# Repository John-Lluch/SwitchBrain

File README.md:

_\[ find below the English translation \]_ 

# SwitchBrain

Documentos y otras utilidades relacionadas con el canal de YouTube del Computador a Relés,

## Canal de YouTube

[https://www.youtube.com/@RelayComputer](https://www.youtube.com/@RelayComputer)

## Enlaces útiles

Kicad EDA : [https://www.kicad.org](https://www.kicad.org)  
Logisim Evolution (simulador digital) edición HC : [https://github.com/kevinawalsh/logisim-evolution](https://github.com/kevinawalsh/logisim-evolution)  
CircuitJS1 (simulador analógico) versión online : [https://www.falstad.com/circuit/circuitjs.html](https://www.falstad.com/circuit/circuitjs.html)  
CircuitJS1 (simulador analógico) versión escritorio : [https://www.falstad.com/circuit/offline/](https://www.falstad.com/circuit/offline/)  

<br /><br />

----------------------------------------------------------------------------------------------------------

# SwitchBrain (English)

Documents and other utilities related with the Relay Computer Youtube Channel

## YouTube Channel

[https://www.youtube.com/@RelayComputer](https://www.youtube.com/@RelayComputer)

## Useful Links

Kicad EDA : [https://www.kicad.org](https://www.kicad.org)  
Logisim Evolution (digital simulator) HC edition : [https://github.com/kevinawalsh/logisim-evolution](https://github.com/kevinawalsh/logisim-evolution)  
CircuitJS1 (analog simulator) online version : [https://www.falstad.com/circuit/circuitjs.html](https://www.falstad.com/circuit/circuitjs.html)  
CircuitJS1 (analog simulator) desktop version : [https://www.falstad.com/circuit/offline/](https://www.falstad.com/circuit/offline/)

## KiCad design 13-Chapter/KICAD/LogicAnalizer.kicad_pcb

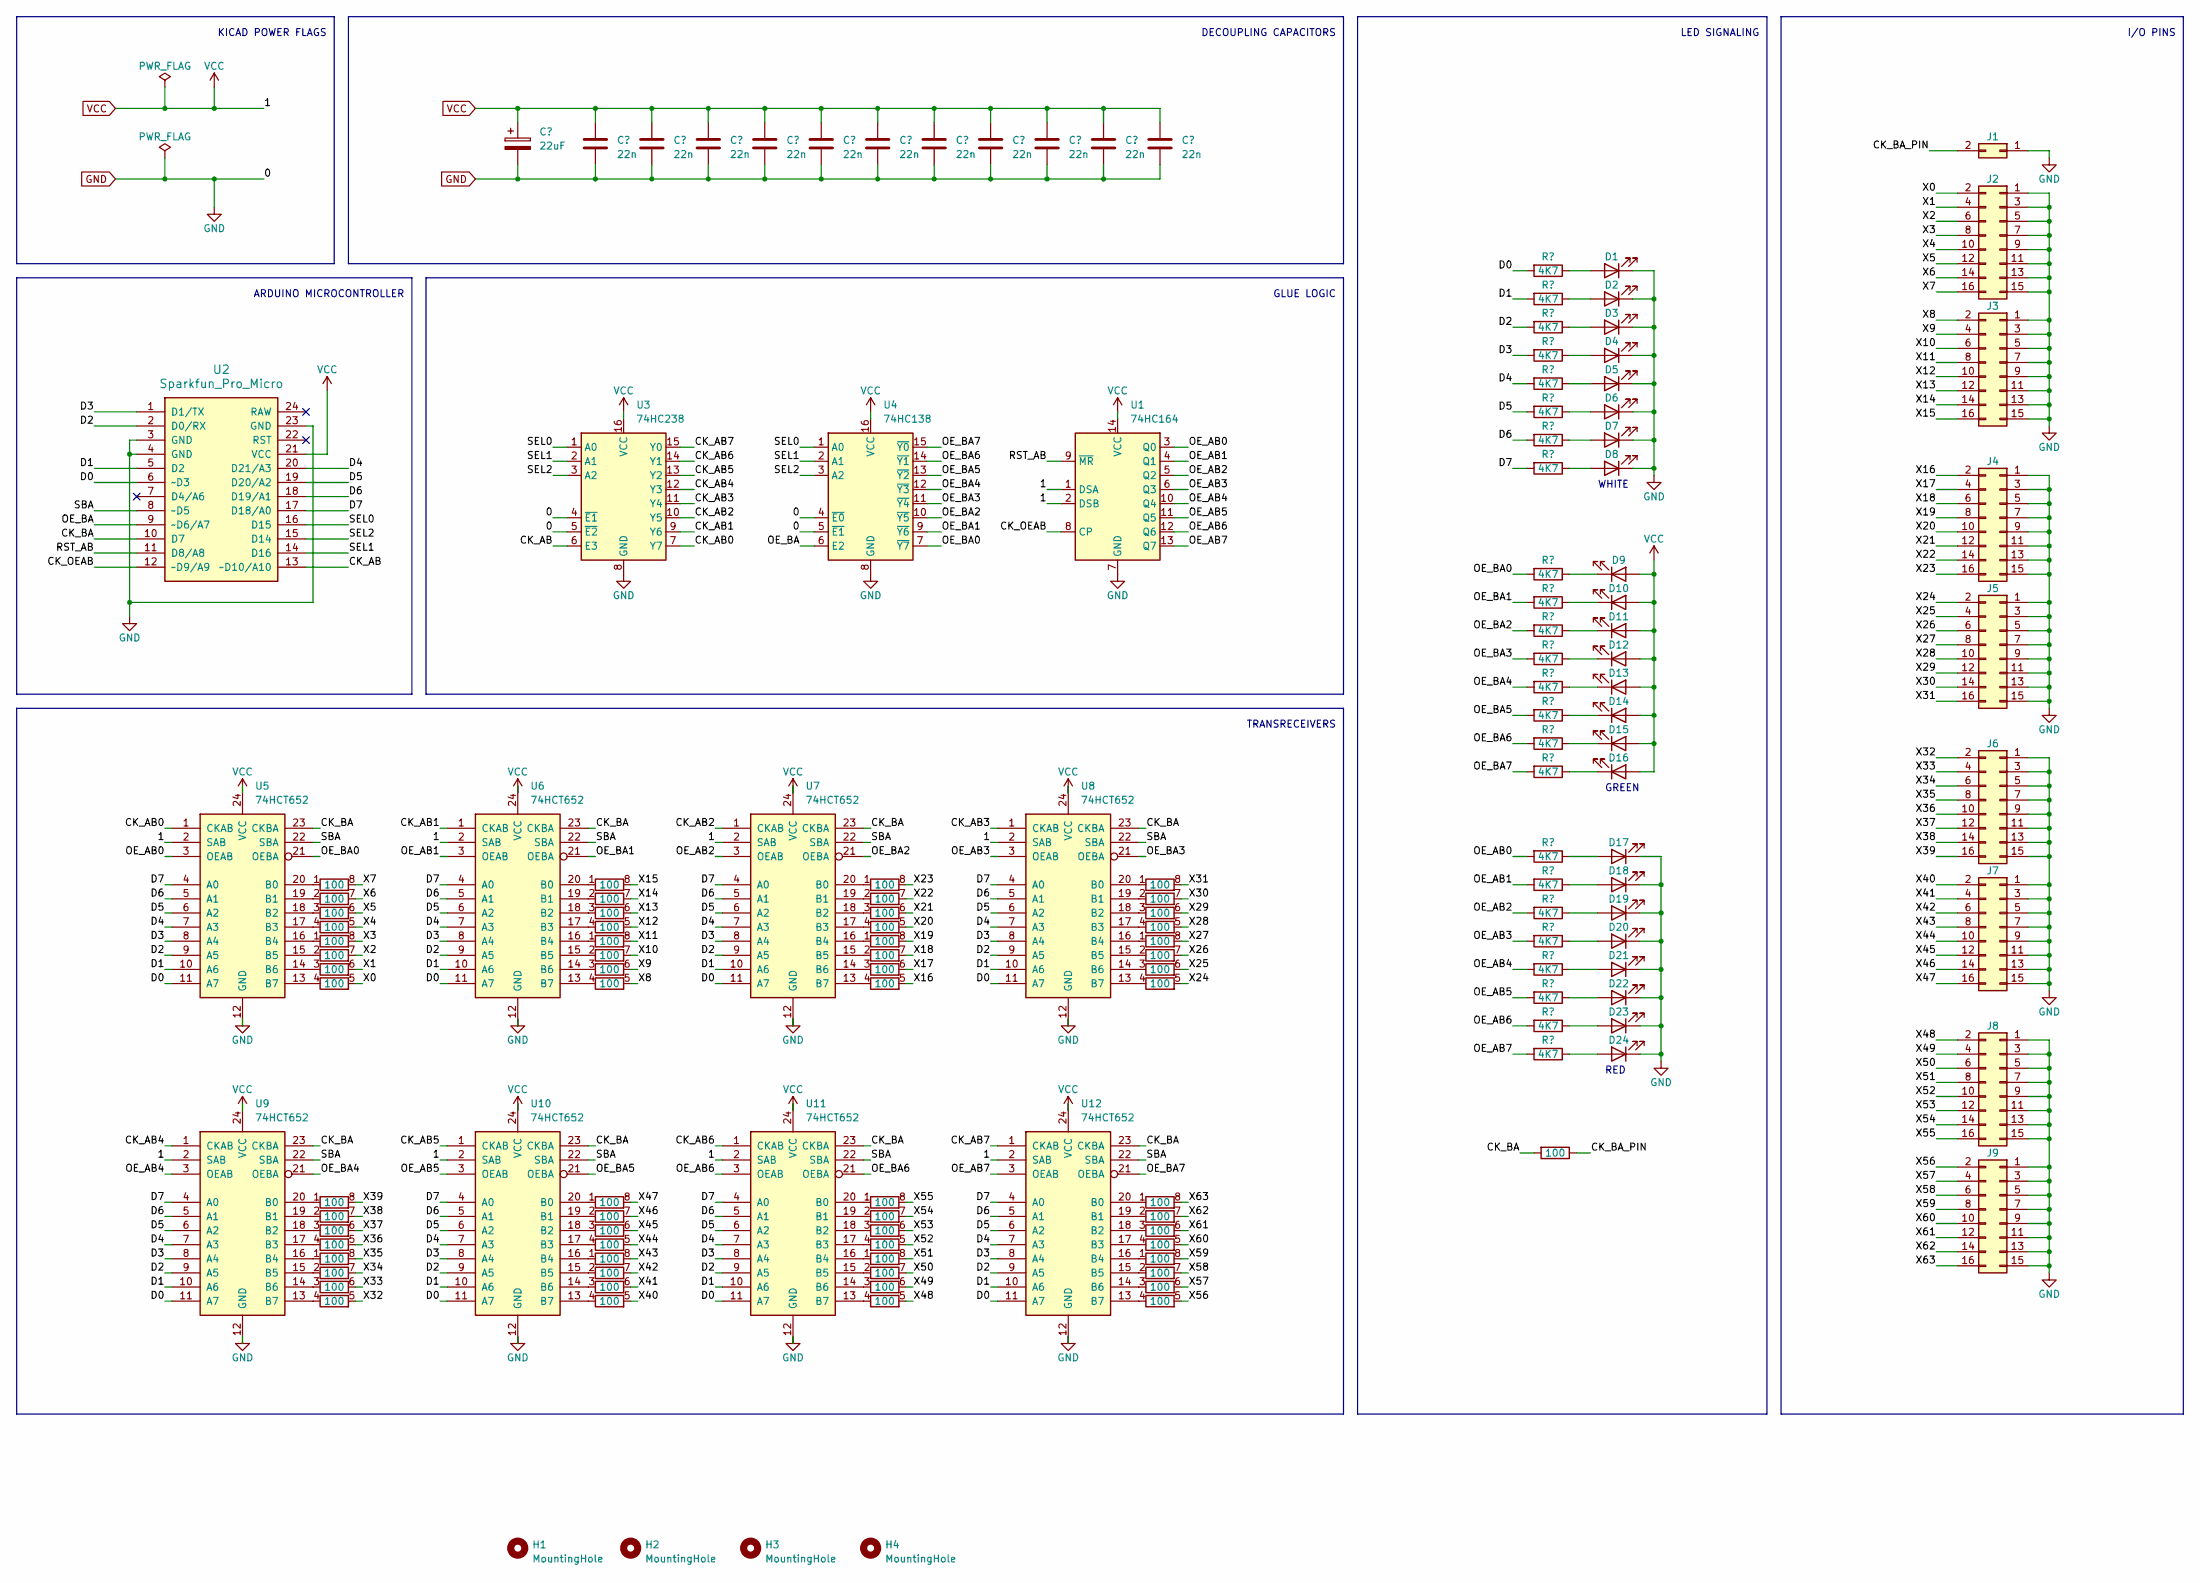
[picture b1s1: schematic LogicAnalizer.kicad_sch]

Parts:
C1: 22uF; CP_Radial_D5.0mm_P2.00mm
C2, C3, C4, C5, C6, C7, C8, C9, C10, C11, C12: 22n; C_0603_1608Metric; LCSC Part # C326840
D1, D2, D3, D4, D5, D6, D7, D8: LED; LED_0603_1608Metric; LCSC Part # C158100
D9, D10, D11, D12, D13, D14, D15, D16: LED; LED_0603_1608Metric; LCSC Part # C89809
D17, D18, D19, D20, D21, D22, D23, D24: LED; LED_0603_1608Metric; LCSC Part # C193902
H1, H2, H3, H4: MountingHole; MountingHole_3.2mm_M3_DIN965_Pad
J1: Conn_02x01; PinHeader_2x01_P2.54mm_Vertical
J2, J3, J4, J5, J6, J7, J8, J9: Conn_02x08_Odd_Even; PinHeader_2x08_P2.54mm_Vertical; LCSC Part # C24328
R1, R2, R3, R4, R5, R6, R7, R8, R9, R10, R11, R12, R13, R14, R15, R16, R17, R18, R19, R20, R21, R22, R23, R24: 4K7; Meu-R_0603_1608Metric; LCSC Part # C23162
R25: 100; Meu-R_0603_1608Metric; LCSC Part # C22775
RN1, RN2, RN3, RN4, RN5, RN6, RN7, RN8, RN9, RN10, RN11, RN12, RN13, RN14, RN15, RN16: 100; R_Array_Convex_4x0603; LCSC Part # C425240
U1: 74HC164; SO-14_3.9x8.65mm_P1.27mm; LCSC Part # C5419
U2: Sparkfun_Pro_Micro
U3: 74HC238; SOIC-16_3.9x9.9mm_P1.27mm; LCSC Part # C68225
U4: 74HC138; SOIC-16_3.9x9.9mm_P1.27mm; LCSC Part # C6818
U5, U6, U7, U8, U9, U10, U11, U12: 74HCT652; SOIC-24W_7.5x15.4mm_P1.27mm

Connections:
/CK_AB: U2.13 (~D10/A10), U3.6 (E3)
/CK_AB0: U3.7 (Y7), U5.1 (CKAB)
/CK_AB1: U3.9 (Y6), U6.1 (CKAB)
/CK_AB2: U3.10 (Y5), U7.1 (CKAB)
/CK_AB3: U3.11 (Y4), U8.1 (CKAB)
/CK_AB4: U3.12 (Y3), U9.1 (CKAB)
/CK_AB5: U3.13 (Y2), U10.1 (CKAB)
/CK_AB6: U3.14 (Y1), U11.1 (CKAB)
/CK_AB7: U3.15 (Y0), U12.1 (CKAB)
/CK_BA: R25.2, U2.10 (D7), U5.23 (CKBA), U6.23 (CKBA), U7.23 (CKBA), U8.23 (CKBA), U9.23 (CKBA), U10.23 (CKBA), U11.23 (CKBA), U12.23 (CKBA)
/CK_BA_PIN: J1.2, R25.1
/CK_OEAB: U1.8 (CP), U2.12 (~D9/A9)
/D0: R1.2, U2.6 (~D3), U5.11 (A7), U6.11 (A7), U7.11 (A7), U8.11 (A7), U9.11 (A7), U10.11 (A7), U11.11 (A7), U12.11 (A7)
/D1: R2.2, U2.5 (D2), U5.10 (A6), U6.10 (A6), U7.10 (A6), U8.10 (A6), U9.10 (A6), U10.10 (A6), U11.10 (A6), U12.10 (A6)
/D2: R3.2, U2.2 (D0/RX), U5.9 (A5), U6.9 (A5), U7.9 (A5), U8.9 (A5), U9.9 (A5), U10.9 (A5), U11.9 (A5), U12.9 (A5)
/D3: R4.2, U2.1 (D1/TX), U5.8 (A4), U6.8 (A4), U7.8 (A4), U8.8 (A4), U9.8 (A4), U10.8 (A4), U11.8 (A4), U12.8 (A4)
/D4: R5.2, U2.20 (D21/A3), U5.7 (A3), U6.7 (A3), U7.7 (A3), U8.7 (A3), U9.7 (A3), U10.7 (A3), U11.7 (A3), U12.7 (A3)
/D5: R6.2, U2.19 (D20/A2), U5.6 (A2), U6.6 (A2), U7.6 (A2), U8.6 (A2), U9.6 (A2), U10.6 (A2), U11.6 (A2), U12.6 (A2)
/D6: R7.2, U2.18 (D19/A1), U5.5 (A1), U6.5 (A1), U7.5 (A1), U8.5 (A1), U9.5 (A1), U10.5 (A1), U11.5 (A1), U12.5 (A1)
/D7: R8.2, U2.17 (D18/A0), U5.4 (A0), U6.4 (A0), U7.4 (A0), U8.4 (A0), U9.4 (A0), U10.4 (A0), U11.4 (A0), U12.4 (A0)
/OE_AB0: R17.2, U1.3 (Q0), U5.3 (OEAB)
/OE_AB1: R18.2, U1.4 (Q1), U6.3 (OEAB)
/OE_AB2: R19.2, U1.5 (Q2), U7.3 (OEAB)
/OE_AB3: R20.2, U1.6 (Q3), U8.3 (OEAB)
/OE_AB4: R21.2, U1.10 (Q4), U9.3 (OEAB)
/OE_AB5: R22.2, U1.11 (Q5), U10.3 (OEAB)
/OE_AB6: R23.2, U1.12 (Q6), U11.3 (OEAB)
/OE_AB7: R24.2, U1.13 (Q7), U12.3 (OEAB)
/OE_BA: U2.9 (~D6/A7), U4.6 (E2)
/OE_BA0: R9.2, U4.7 (~Y7), U5.21 (OEBA)
/OE_BA1: R10.2, U4.9 (~Y6), U6.21 (OEBA)
/OE_BA2: R11.2, U4.10 (~Y5), U7.21 (OEBA)
/OE_BA3: R12.2, U4.11 (~Y4), U8.21 (OEBA)
/OE_BA4: R13.2, U4.12 (~Y3), U9.21 (OEBA)
/OE_BA5: R14.2, U4.13 (~Y2), U10.21 (OEBA)
/OE_BA6: R15.2, U4.14 (~Y1), U11.21 (OEBA)
/OE_BA7: R16.2, U4.15 (~Y0), U12.21 (OEBA)
/RST_AB: U1.9 (~MR), U2.11 (D8/A8)
/SBA: U2.8 (~D5), U5.22 (SBA), U6.22 (SBA), U7.22 (SBA), U8.22 (SBA), U9.22 (SBA), U10.22 (SBA), U11.22 (SBA), U12.22 (SBA)
/SEL0: U2.16 (D15), U3.1 (A0), U4.1 (A0)
/SEL1: U2.14 (D16), U3.2 (A1), U4.2 (A1)
/SEL2: U2.15 (D14), U3.3 (A2), U4.3 (A2)
/X0: J2.2, RN5.5 (R4.2)
/X1: J2.4, RN5.6 (R3.2)
/X2: J2.6, RN5.7 (R2.2)
/X3: J2.8, RN5.8 (R1.2)
/X4: J2.10, RN1.5 (R4.2)
/X5: J2.12, RN1.6 (R3.2)
/X6: J2.14, RN1.7 (R2.2)
/X7: J2.16, RN1.8 (R1.2)
/X8: J3.2, RN6.5 (R4.2)
/X9: J3.4, RN6.6 (R3.2)
/X10: J3.6, RN6.7 (R2.2)
/X11: J3.8, RN6.8 (R1.2)
/X12: J3.10, RN2.5 (R4.2)
/X13: J3.12, RN2.6 (R3.2)
/X14: J3.14, RN2.7 (R2.2)
/X15: J3.16, RN2.8 (R1.2)
/X16: J4.2, RN7.5 (R4.2)
/X17: J4.4, RN7.6 (R3.2)
/X18: J4.6, RN7.7 (R2.2)
/X19: J4.8, RN7.8 (R1.2)
/X20: J4.10, RN3.5 (R4.2)
/X21: J4.12, RN3.6 (R3.2)
/X22: J4.14, RN3.7 (R2.2)
/X23: J4.16, RN3.8 (R1.2)
/X24: J5.2, RN8.5 (R4.2)
/X25: J5.4, RN8.6 (R3.2)
/X26: J5.6, RN8.7 (R2.2)
/X27: J5.8, RN8.8 (R1.2)
/X28: J5.10, RN4.5 (R4.2)
/X29: J5.12, RN4.6 (R3.2)
/X30: J5.14, RN4.7 (R2.2)
/X31: J5.16, RN4.8 (R1.2)
/X32: J6.2, RN13.5 (R4.2)
/X33: J6.4, RN13.6 (R3.2)
/X34: J6.6, RN13.7 (R2.2)
/X35: J6.8, RN13.8 (R1.2)
/X36: J6.10, RN9.5 (R4.2)
/X37: J6.12, RN9.6 (R3.2)
/X38: J6.14, RN9.7 (R2.2)
/X39: J6.16, RN9.8 (R1.2)
/X40: J7.2, RN14.5 (R4.2)
/X41: J7.4, RN14.6 (R3.2)
/X42: J7.6, RN14.7 (R2.2)
/X43: J7.8, RN14.8 (R1.2)
/X44: J7.10, RN10.5 (R4.2)
/X45: J7.12, RN10.6 (R3.2)
/X46: J7.14, RN10.7 (R2.2)
/X47: J7.16, RN10.8 (R1.2)
/X48: J8.2, RN15.5 (R4.2)
/X49: J8.4, RN15.6 (R3.2)
/X50: J8.6, RN15.7 (R2.2)
/X51: J8.8, RN15.8 (R1.2)
/X52: J8.10, RN11.5 (R4.2)
/X53: J8.12, RN11.6 (R3.2)
/X54: J8.14, RN11.7 (R2.2)
/X55: J8.16, RN11.8 (R1.2)
/X56: J9.2, RN16.5 (R4.2)
/X57: J9.4, RN16.6 (R3.2)
/X58: J9.6, RN16.7 (R2.2)
/X59: J9.8, RN16.8 (R1.2)
/X60: J9.10, RN12.5 (R4.2)
/X61: J9.12, RN12.6 (R3.2)
/X62: J9.14, RN12.7 (R2.2)
/X63: J9.16, RN12.8 (R1.2)
GND: C1.2, C2.2, C3.2, C4.2, C5.2, C6.2, C7.2, C8.2, C9.2, C10.2, C11.2, C12.2, D1.1 (K), D2.1 (K), D3.1 (K), D4.1 (K), D5.1 (K), D6.1 (K), D7.1 (K), D8.1 (K), D17.1 (K), D18.1 (K), D19.1 (K), D20.1 (K), D21.1 (K), D22.1 (K), D23.1 (K), D24.1 (K), J1.1, J2.1, J2.3, J2.5, J2.7, J2.9, J2.11, J2.13, J2.15, J3.1, J3.3, J3.5, J3.7, J3.9, J3.11, J3.13, J3.15, J4.1, J4.3, J4.5, J4.7, J4.9, J4.11, J4.13, J4.15, J5.1, J5.3, J5.5, J5.7, J5.9, J5.11, J5.13, J5.15, J6.1, J6.3, J6.5, J6.7, J6.9, J6.11, J6.13, J6.15, J7.1, J7.3, J7.5, J7.7, J7.9, J7.11, J7.13, J7.15, J8.1, J8.3, J8.5, J8.7, J8.9, J8.11, J8.13, J8.15, J9.1, J9.3, J9.5, J9.7, J9.9, J9.11, J9.13, J9.15, U1.7 (GND), U2.3 (GND), U2.4 (GND), U2.23 (GND), U3.4 (~E1), U3.5 (~E2), U3.8 (GND), U4.4 (~E0), U4.5 (~E1), U4.8 (GND), U5.12 (GND), U6.12 (GND), U7.12 (GND), U8.12 (GND), U9.12 (GND), U10.12 (GND), U11.12 (GND), U12.12 (GND)
unnamed: D1.2 (A), R1.1
unnamed: D2.2 (A), R2.1
unnamed: D3.2 (A), R3.1
unnamed: D4.2 (A), R4.1
unnamed: D5.2 (A), R5.1
unnamed: D6.2 (A), R6.1
unnamed: D7.2 (A), R7.1
unnamed: D8.2 (A), R8.1
unnamed: D9.1 (K), R9.1
unnamed: D10.1 (K), R10.1
unnamed: D11.1 (K), R11.1
unnamed: D12.1 (K), R12.1
unnamed: D13.1 (K), R13.1
unnamed: D14.1 (K), R14.1
unnamed: D15.1 (K), R15.1
unnamed: D16.1 (K), R16.1
unnamed: D17.2 (A), R17.1
unnamed: D18.2 (A), R18.1
unnamed: D19.2 (A), R19.1
unnamed: D20.2 (A), R20.1
unnamed: D21.2 (A), R21.1
unnamed: D22.2 (A), R22.1
unnamed: D23.2 (A), R23.1
unnamed: D24.2 (A), R24.1
unnamed: RN1.1 (R1.1), U5.20 (B0)
unnamed: RN1.2 (R2.1), U5.19 (B1)
unnamed: RN1.3 (R3.1), U5.18 (B2)
unnamed: RN1.4 (R4.1), U5.17 (B3)
unnamed: RN2.1 (R1.1), U6.20 (B0)
unnamed: RN2.2 (R2.1), U6.19 (B1)
unnamed: RN2.3 (R3.1), U6.18 (B2)
unnamed: RN2.4 (R4.1), U6.17 (B3)
unnamed: RN3.1 (R1.1), U7.20 (B0)
unnamed: RN3.2 (R2.1), U7.19 (B1)
unnamed: RN3.3 (R3.1), U7.18 (B2)
unnamed: RN3.4 (R4.1), U7.17 (B3)
unnamed: RN4.1 (R1.1), U8.20 (B0)
unnamed: RN4.2 (R2.1), U8.19 (B1)
unnamed: RN4.3 (R3.1), U8.18 (B2)
unnamed: RN4.4 (R4.1), U8.17 (B3)
unnamed: RN5.1 (R1.1), U5.16 (B4)
unnamed: RN5.2 (R2.1), U5.15 (B5)
unnamed: RN5.3 (R3.1), U5.14 (B6)
unnamed: RN5.4 (R4.1), U5.13 (B7)
unnamed: RN6.1 (R1.1), U6.16 (B4)
unnamed: RN6.2 (R2.1), U6.15 (B5)
unnamed: RN6.3 (R3.1), U6.14 (B6)
unnamed: RN6.4 (R4.1), U6.13 (B7)
unnamed: RN7.1 (R1.1), U7.16 (B4)
unnamed: RN7.2 (R2.1), U7.15 (B5)
unnamed: RN7.3 (R3.1), U7.14 (B6)
unnamed: RN7.4 (R4.1), U7.13 (B7)
unnamed: RN8.1 (R1.1), U8.16 (B4)
unnamed: RN8.2 (R2.1), U8.15 (B5)
unnamed: RN8.3 (R3.1), U8.14 (B6)
unnamed: RN8.4 (R4.1), U8.13 (B7)
unnamed: RN9.1 (R1.1), U9.20 (B0)
unnamed: RN9.2 (R2.1), U9.19 (B1)
unnamed: RN9.3 (R3.1), U9.18 (B2)
unnamed: RN9.4 (R4.1), U9.17 (B3)
unnamed: RN10.1 (R1.1), U10.20 (B0)
unnamed: RN10.2 (R2.1), U10.19 (B1)
unnamed: RN10.3 (R3.1), U10.18 (B2)
unnamed: RN10.4 (R4.1), U10.17 (B3)
unnamed: RN11.1 (R1.1), U11.20 (B0)
unnamed: RN11.2 (R2.1), U11.19 (B1)
unnamed: RN11.3 (R3.1), U11.18 (B2)
unnamed: RN11.4 (R4.1), U11.17 (B3)
unnamed: RN12.1 (R1.1), U12.20 (B0)
unnamed: RN12.2 (R2.1), U12.19 (B1)
unnamed: RN12.3 (R3.1), U12.18 (B2)
unnamed: RN12.4 (R4.1), U12.17 (B3)
unnamed: RN13.1 (R1.1), U9.16 (B4)
unnamed: RN13.2 (R2.1), U9.15 (B5)
unnamed: RN13.3 (R3.1), U9.14 (B6)
unnamed: RN13.4 (R4.1), U9.13 (B7)
unnamed: RN14.1 (R1.1), U10.16 (B4)
unnamed: RN14.2 (R2.1), U10.15 (B5)
unnamed: RN14.3 (R3.1), U10.14 (B6)
unnamed: RN14.4 (R4.1), U10.13 (B7)
unnamed: RN15.1 (R1.1), U11.16 (B4)
unnamed: RN15.2 (R2.1), U11.15 (B5)
unnamed: RN15.3 (R3.1), U11.14 (B6)
unnamed: RN15.4 (R4.1), U11.13 (B7)
unnamed: RN16.1 (R1.1), U12.16 (B4)
unnamed: RN16.2 (R2.1), U12.15 (B5)
unnamed: RN16.3 (R3.1), U12.14 (B6)
unnamed: RN16.4 (R4.1), U12.13 (B7)
VCC: C1.1, C2.1, C3.1, C4.1, C5.1, C6.1, C7.1, C8.1, C9.1, C10.1, C11.1, C12.1, D9.2 (A), D10.2 (A), D11.2 (A), D12.2 (A), D13.2 (A), D14.2 (A), D15.2 (A), D16.2 (A), U1.1 (DSA), U1.2 (DSB), U1.14 (VCC), U2.21 (VCC), U3.16 (VCC), U4.16 (VCC), U5.2 (SAB), U5.24 (VCC), U6.2 (SAB), U6.24 (VCC), U7.2 (SAB), U7.24 (VCC), U8.2 (SAB), U8.24 (VCC), U9.2 (SAB), U9.24 (VCC), U10.2 (SAB), U10.24 (VCC), U11.2 (SAB), U11.24 (VCC), U12.2 (SAB), U12.24 (VCC)

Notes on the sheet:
TRANSRECEIVERS
ARDUINO MICROCONTROLLER
DECOUPLING CAPACITORS
LED SIGNALING
GLUE LOGIC
WHITE
I/O PINS
RED
KICAD POWER FLAGS
GREEN

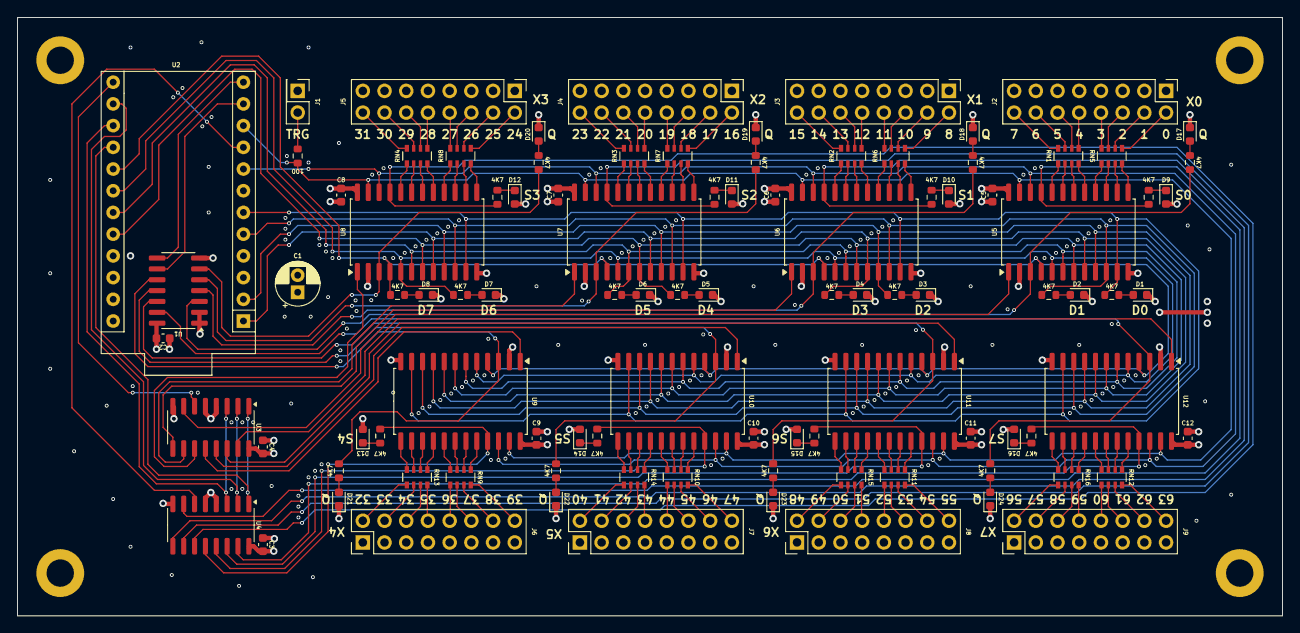
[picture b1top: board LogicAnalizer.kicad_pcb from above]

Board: 4 copper layers, 148.0 x 70.0 mm, 102 parts (0 on the bottom side), 196 nets.

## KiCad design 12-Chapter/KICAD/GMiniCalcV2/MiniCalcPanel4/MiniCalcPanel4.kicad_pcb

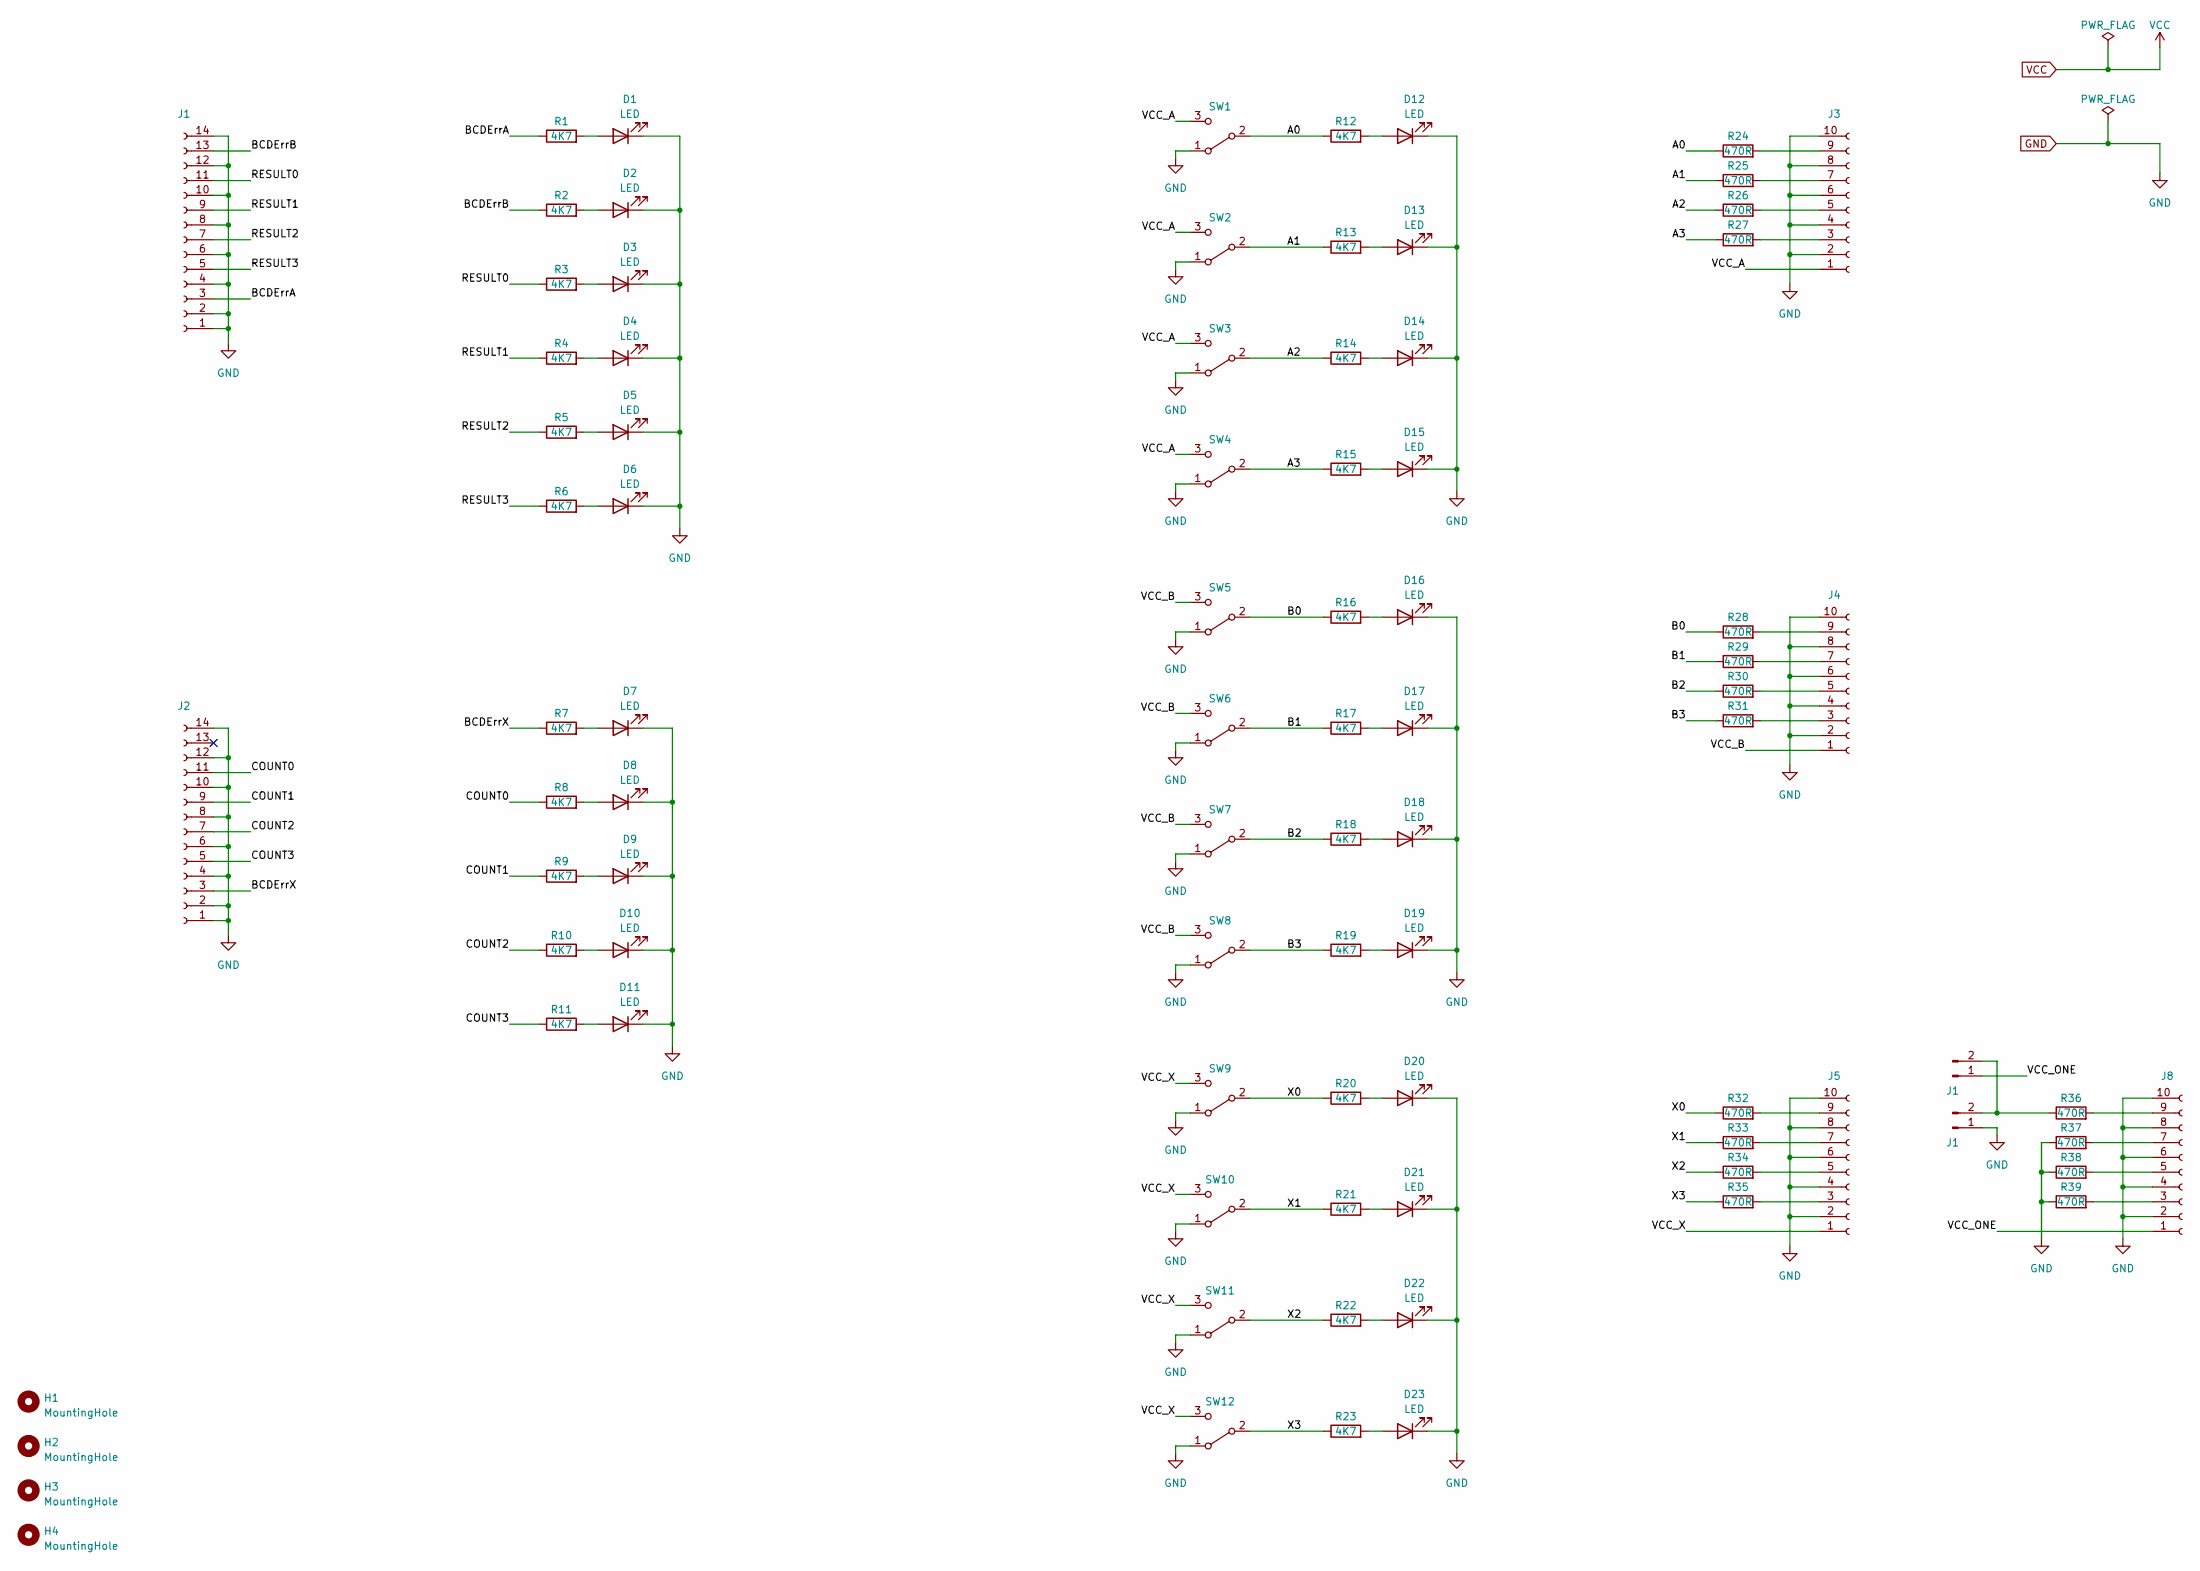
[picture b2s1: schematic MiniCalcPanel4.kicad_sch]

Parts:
D1, D2, D3, D4, D5, D6, D7, D8, D9, D10, D11, D12, D13, D14, D15, D16, D17, D18, D19, D20, D21, D22, D23: LED; LED_D3.0mm_Centrat
H1, H2, H3, H4: MountingHole; MountingHole_3.2mm_M3_DIN965_Pad
J1: Conn_01x02_Pin; SolderJumper-2_P1.3mm_Open_RoundedPad1.0x1.5mm
J2: Conn_01x14_Socket; PinHeader_2x07_P2.54mm_Vertical
J3, J4, J5, J8: Conn_01x10_Socket; PinHeader_2x05_P2.54mm_Vertical
R1, R2, R3, R4, R5, R6, R7, R8, R9, R10, R11, R12, R13, R14, R15, R16, R17, R18, R19, R20, R21, R22, R23: 4K7; R_Axial_DIN0207_L6.3mm_D2.5mm_P7.62mm_Horizontal
R24, R25, R26, R27, R28, R29, R30, R31, R32, R33, R34, R35, R36, R37, R38, R39: 470R; R_Axial_DIN0207_L6.3mm_D2.5mm_P7.62mm_Horizontal
SW1, SW2, SW3, SW4, SW5, SW6, SW7, SW8, SW9, SW10, SW11, SW12: SW_SPDT; SW_Toggle_SPDT_Vertical_Mini

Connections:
/A0: R12.1, R24.1, SW1.2 (B)
/A1: R13.1, R25.1, SW2.2 (B)
/A2: R14.1, R26.1, SW3.2 (B)
/A3: R15.1, R27.1, SW4.2 (B)
/B0: R16.1, R28.1, SW5.2 (B)
/B1: R17.1, R29.1, SW6.2 (B)
/B2: R18.1, R30.1, SW7.2 (B)
/B3: R19.1, R31.1, SW8.2 (B)
/BCDErrA: J1.3, R1.1
/BCDErrB: J1.13, R2.1
/BCDErrX: J2.3, R7.1
/COUNT0: J2.11, R8.1
/COUNT1: J2.9, R9.1
/COUNT2: J2.7, R10.1
/COUNT3: J2.5, R11.1
/RESULT0: J1.11, R3.1
/RESULT1: J1.9, R4.1
/RESULT2: J1.7, R5.1
/RESULT3: J1.5, R6.1
/VCC_A: J3.1, SW1.3 (C), SW2.3 (C), SW3.3 (C), SW4.3 (C)
/VCC_B: J4.1, SW5.3 (C), SW6.3 (C), SW7.3 (C), SW8.3 (C)
/VCC_X: J5.1, SW9.3 (C), SW10.3 (C), SW11.3 (C), SW12.3 (C)
/X0: R20.1, R32.1, SW9.2 (B)
/X1: R21.1, R33.1, SW10.2 (B)
/X2: R22.1, R34.1, SW11.2 (B)
/X3: R23.1, R35.1, SW12.2 (B)
unnamed: D1.2 (A), R1.2
unnamed: D2.2 (A), R2.2
unnamed: D3.2 (A), R3.2
unnamed: D4.2 (A), R4.2
unnamed: D5.2 (A), R5.2
unnamed: D6.2 (A), R6.2
unnamed: D7.2 (A), R7.2
unnamed: D8.2 (A), R8.2
unnamed: D9.2 (A), R9.2
unnamed: D10.2 (A), R10.2
unnamed: D11.2 (A), R11.2
unnamed: D12.2 (A), R12.2
unnamed: D13.2 (A), R13.2
unnamed: D14.2 (A), R14.2
unnamed: D15.2 (A), R15.2
unnamed: D16.2 (A), R16.2
unnamed: D17.2 (A), R17.2
unnamed: D18.2 (A), R18.2
unnamed: D19.2 (A), R19.2
unnamed: D20.2 (A), R20.2
unnamed: D21.2 (A), R21.2
unnamed: D22.2 (A), R22.2
unnamed: D23.2 (A), R23.2
unnamed: J3.3, R27.2
unnamed: J3.5, R26.2
unnamed: J3.7, R25.2
unnamed: J3.9, R24.2
unnamed: J4.3, R31.2
unnamed: J4.5, R30.2
unnamed: J4.7, R29.2
unnamed: J4.9, R28.2
unnamed: J5.3, R35.2
unnamed: J5.5, R34.2
unnamed: J5.7, R33.2
unnamed: J5.9, R32.2
unnamed: J8.3, R39.2
unnamed: J8.5, R38.2
unnamed: J8.7, R37.2
unnamed: J8.9, R36.2

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
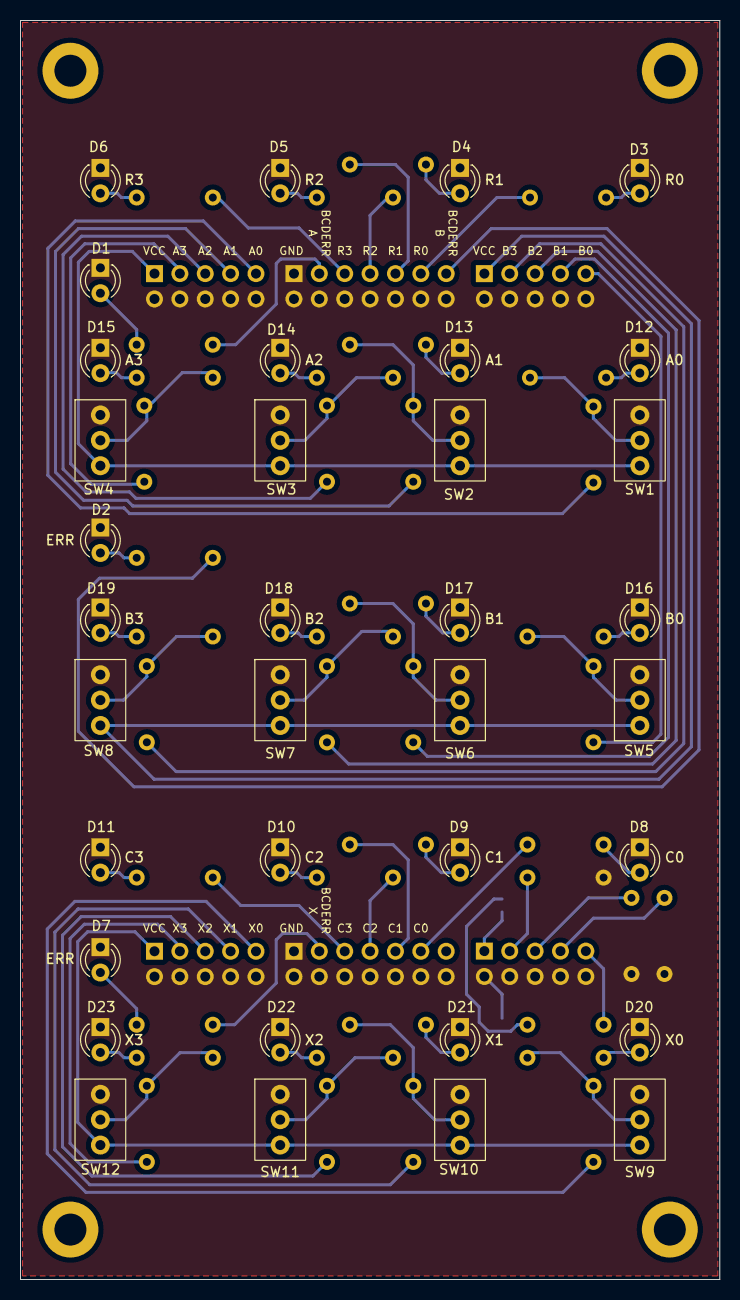
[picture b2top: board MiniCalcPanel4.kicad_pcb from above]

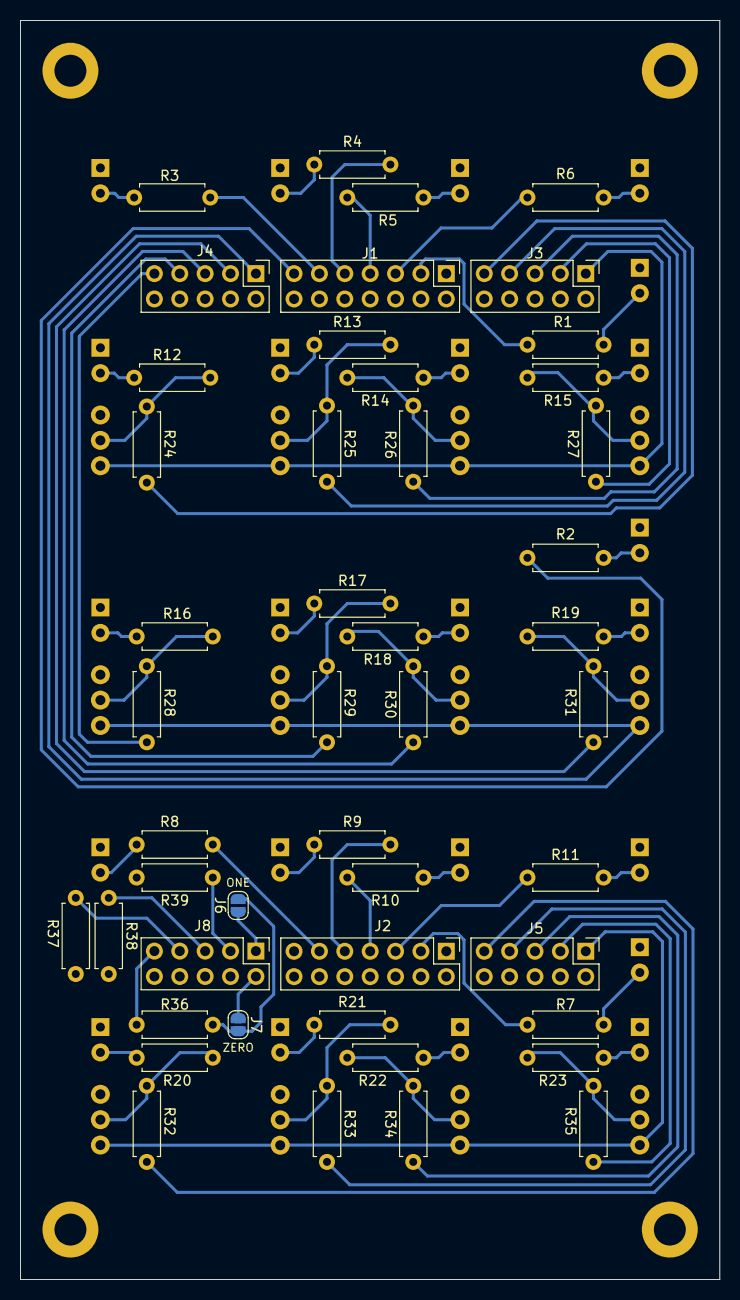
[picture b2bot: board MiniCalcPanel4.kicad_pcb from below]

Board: 2 copper layers, 70.0 x 126.0 mm, 86 parts (47 on the bottom side), 68 nets.

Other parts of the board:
J6, J7: Conn_01x02_Pin; SolderJumper-2_P1.3mm_Open_RoundedPad1.0x1.5mm

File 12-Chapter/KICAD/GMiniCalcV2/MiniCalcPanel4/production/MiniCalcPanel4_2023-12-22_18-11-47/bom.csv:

Designator,Footprint,Quantity,Value,LCSC Part #
"D1, D10, D11, D12, D13, D14, D15, D16, D17, D18, D19, D2, D20, D21, D22, D23, D3, D4, D5, D6, D7, D8, D9",LED_D3.0mm_Centrat,23,LED,
"H1, H2, H3, H4",MountingHole_3.2mm_M3_DIN965_Pad,4,MountingHole,
"J1, J2",PinHeader_2x07_P2.54mm_Vertical,2,Conn_01x14_Socket,
"J3, J4, J5, J8",PinHeader_2x05_P2.54mm_Vertical,4,Conn_01x10_Socket,
"J6, J7",SolderJumper-2_P1.3mm_Open_RoundedPad1.0x1.5mm,2,Conn_01x02_Pin,
"R1, R10, R11, R12, R13, R14, R15, R16, R17, R18, R19, R2, R20, R21, R22, R23, R3, R4, R5, R6, R7, R8, R9",R_Axial_DIN0207_L6.3mm_D2.5mm_P7.62mm_Horizontal,23,4K7,
"R24, R25, R26, R27, R28, R29, R30, R31, R32, R33, R34, R35, R36, R37, R38, R39",R_Axial_DIN0207_L6.3mm_D2.5mm_P7.62mm_Horizontal,16,470R,
"SW1, SW10, SW11, SW12, SW2, SW3, SW4, SW5, SW6, SW7, SW8, SW9",SW_Toggle_SPDT_Vertical_Mini,12,SW_SPDT,

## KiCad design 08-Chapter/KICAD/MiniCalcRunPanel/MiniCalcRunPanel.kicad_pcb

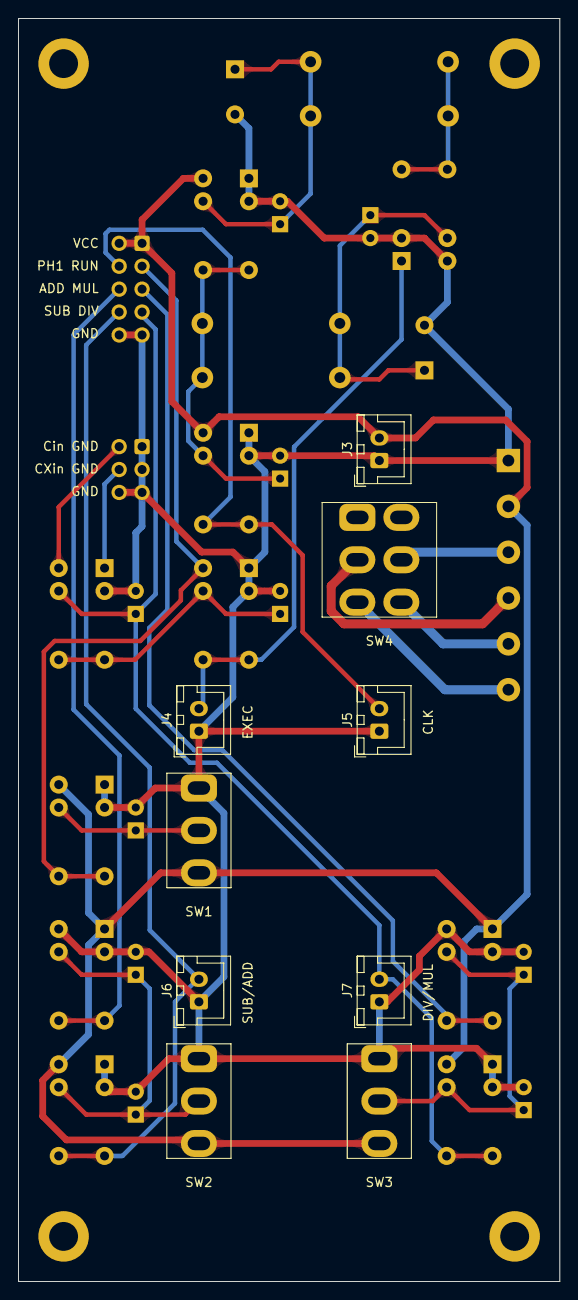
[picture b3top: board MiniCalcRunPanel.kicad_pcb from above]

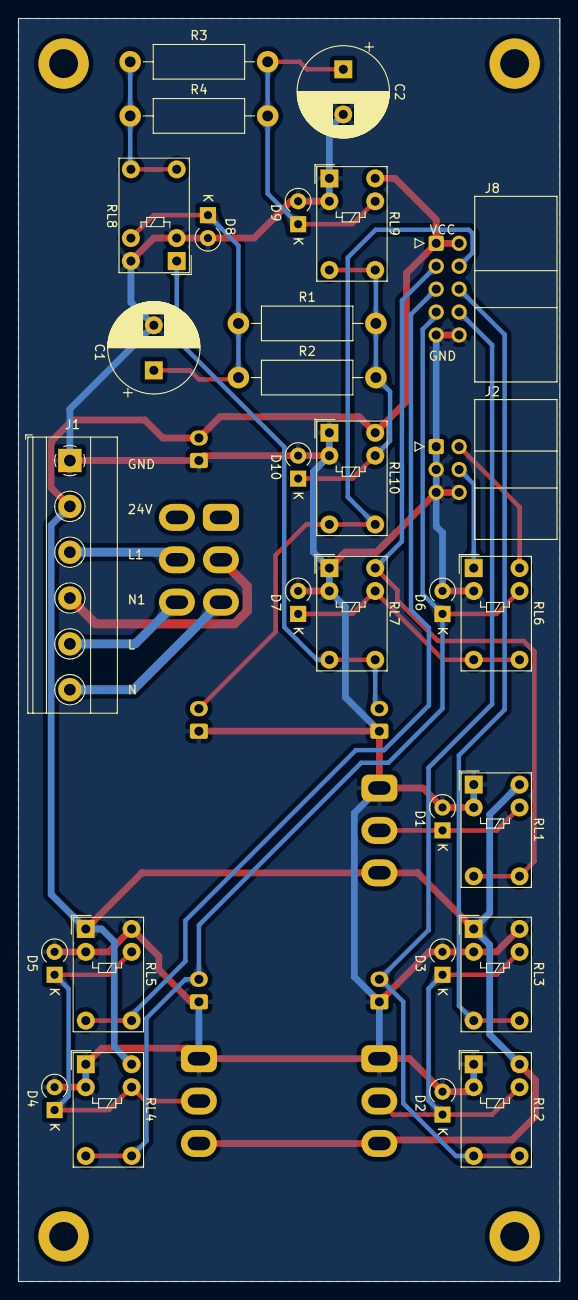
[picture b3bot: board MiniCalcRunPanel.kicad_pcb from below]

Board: 2 copper layers, 60.0 x 140.0 mm, 42 parts (29 on the bottom side), 23 nets.

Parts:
C1, C2: 220u; CP_Radial_D10.0mm_P5.00mm
D1, D2, D3, D4, D5, D6, D7, D8, D9, D10: 1N4007_FLYB; D_A-405_P2.54mm_Vertical_KathodeUp
H1, H2, H3, H4: MountingHole; MountingHole_3.2mm_M3_DIN965_Pad
J1: Conn_01x06_Socket; TerminalBlock_Phoenix_MKDS-1,5-6-5.08_1x06_P5.08mm_Horizont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
J2: Conn_01x06_Pin; IDC-Header_2x03_P2.54mm_Horizontal
J3: Power; JST_XH_B2B-XH-A_1x02_P2.50mm_Vertical
J4, J5, J6, J7: Conn_01x02_Pin; JST_XH_B2B-XH-A_1x02_P2.50mm_Vertical
J8: Conn_01x10_Pin; IDC-Header_2x05_P2.54mm_Horizontal
R1, R2, R3, R4: 220; R_Axial_DIN0411_L9.9mm_D3.6mm_P15.24mm_Horizontal
RL1, RL2, RL3, RL4, RL5, RL6, RL7, RL8, RL9, RL10: G5V-1; Relay_SPDT_Omron_G5V-1_girat
SW1, SW2, SW3: SW_SPDT; SW_Toggle_SPDT_Vertical_Oval
SW4: SW_DPDT; SW_Toggle_DPDT_Vertical_Oval

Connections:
ADD: J8.6, RL3.5, RL3.6
CLK: J5.2, J8.4, RL10.5, RL10.6
CXin: J2.4, RL6.1
Cin: J2.2, RL6.10
DIV: D6.1, J7.2, J8.7, RL4.5, RL4.6, RL6.9
EXE: J4.2, RL7.5, RL7.6, RL8.1
GND: C1.2, C2.2, D1.2 (GND), D2.2 (GND), D3.2 (GND), D4.2 (GND), D5.2 (GND), D6.2 (GND), D7.2 (GND), D8.2 (GND), D9.2 (GND), D10.2 (GND), J1.1, J2.1, J2.3, J2.5, J2.6, J3.1, J4.1, J5.1, J6.1, J7.1, J8.9, J8.10, RL1.1, RL1.2 (GND), RL2.1, RL2.2 (GND), RL3.2 (GND), RL3.10, RL4.1, RL4.2 (GND), RL5.2 (GND), RL5.10, RL6.2 (GND), RL7.1, RL7.2 (GND), RL8.2 (GND), RL8.10, RL9.1, RL9.2 (GND), RL10.1, RL10.2 (GND), SW1.1 (A), SW2.1 (A), SW3.1 (A)
MUL: J8.5, RL5.5, RL5.6
unnamed: C1.1, D8.1, R1.1, R2.1, RL8.9
unnamed: C2.1, D9.1, R3.2, R4.2, RL9.9
unnamed: D7.1, RL6.5, RL6.6, RL7.9
unnamed: D10.1, R1.2, R2.2, RL9.5, RL9.6, RL10.9
unnamed: J1.3, SW4.5 (E)
unnamed: J1.4, SW4.2 (B)
unnamed: J1.5, SW4.6 (F)
unnamed: J1.6, SW4.3 (C)
unnamed: R3.1, R4.1, RL8.5, RL8.6
unnamed: D1.1, RL1.9, SW1.2 (B)
unnamed: D2.1, D3.1, RL2.9, RL3.9, SW2.2 (B)
unnamed: D4.1, D5.1, RL4.9, RL5.9, SW3.2 (B)
RUN: J8.3, RL1.5, RL1.6, RL7.10
SUB: J6.2, J8.8, RL2.5, RL2.6
VCC: J1.2, J3.2, J8.1, J8.2, RL1.10, RL2.10, RL3.1, RL4.10, RL5.1, RL9.10, RL10.10, SW1.3 (C), SW2.3 (C), SW3.3 (C)
